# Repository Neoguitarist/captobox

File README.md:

**Introduction**

Ce GitHub est basé sur celui de Julien Rat : https://github.com/julienrat/captobox .

Le code a été fortement restructuré, et de nouveaux capteurs sont pris en charge.

**Capteurs pris en charge actuellement**

- M0D1023 (incluant BME280 et iAQ) :
	- MOD1023 : http://www.embeddedadventures.com/bme280_AMS-IAQ_multi_sensor_mod-1023.html
	- BME280 : https://www.bluedot.space/sensor-boards/bme280/
- BME680 : https://joy-it.net/en/products/SEN-BME680
- CCS811 : https://joy-it.net/en/products/SEN-CCS811V1

**Prise en main**

Dans le dossier "resources/prise en main", vous trouverez deux documents essentiels :
- "Description matos.pdf" : liste avec photos de l'ensemble du matériel constituant une Captobox.
- "Branchements captobox.pdf" : guide pour le branchement des différents capteurs sur le module cerveau.

**Note importante**

À l'heure actuelle, il est nécessaire de redémarrer la carte lorsqu'on change de capteur, pour que celui-ci soit détecté.

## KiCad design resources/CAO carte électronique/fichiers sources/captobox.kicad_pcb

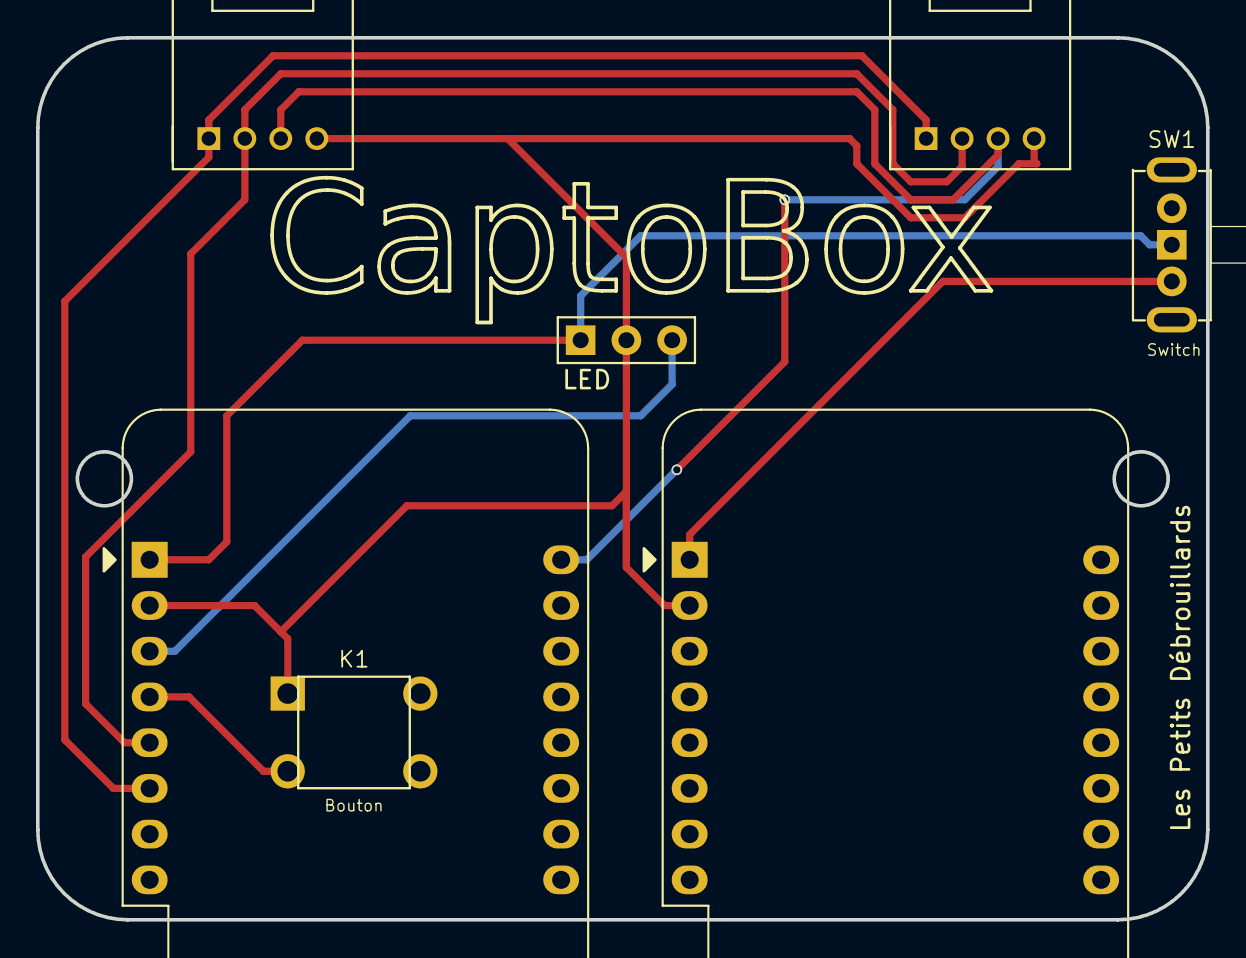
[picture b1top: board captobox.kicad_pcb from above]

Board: 2 copper layers, 65.0 x 49.0 mm, 7 parts (0 on the bottom side), 8 nets.

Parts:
BAT1: Shield_bat; WEMOS_D1_mini_light2
J1, J2: GROVE-CONNECTOR-DIP-90D_4P-2.0_; HW4-2.0-90D
K1: Bouton; SW4-6.0X6.0X5.0MM
LED: DIP-BLACK-MALE-HEADER-VERT_3P-2.54_; H3-2.54
SW1: Switch; SW5-2.0-8.8X4.4X4.7MM-90D
Wemos1: WeMos_mini; WEMOS_D1_mini_light2

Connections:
3,3V: J1.3, J2.3, Wemos1.16
5V: LED.1, SW1.COM, Wemos1.1
D3: K1.2, Wemos1.4
D4: LED.3, Wemos1.3
GND: BAT1.2, J1.4, J2.4, K1.1, LED.2, Wemos1.2
GPIO4: J1.2, J2.2, Wemos1.5
GPIO5: J1.1, J2.1, Wemos1.6
VCC: BAT1.1, SW1.B

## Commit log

2020-03-02 Reprise des sources de https://github.com/julienrat/captobox . Restructuration du code.
2020-03-02 Ajout d'une doc sur l'électroniquue
2020-03-06 Code avec implémentation du ccs811
2020-03-06 simple program de test pour le ccs811
2020-03-06 Poursuite de la refactorisation du code : maintenant, tout compile, et les capteurs MOD1023 et BME680 sont de nouveau utilisables ! Mise à jour du .gitignore pour ne plus conserver les produits de co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
2020-03-06 MAJ readme
2020-03-07 Implémentation de la prise en charge du capteur CCS811. Ajout d'un dossier "docs", contenant les manuels des capteurs BME680 et CCS811, ainsi que des aides concernant la captobox.
2020-03-08 Refacto du fichier config.js.
2020-03-08 Refacto de config.html.
2020-03-08 Simplification du CSS. Suppression des fichiers inutiles dans le dossier data. Simplification et clarification du dossier data.
2020-03-13 Docs/tuto pour la construction de la captobox
2020-03-18 Ajout de commentaires dans le code. Ajout de fichiers de ressources (CAO et autres). Réorganisation des dossiers.
2020-03-18 Déplacement des documents de prise en main.
